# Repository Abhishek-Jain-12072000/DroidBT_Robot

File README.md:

# DROIDBT_Robot
 Self-propelled robot controlled via a dedicated application in Andoid system.

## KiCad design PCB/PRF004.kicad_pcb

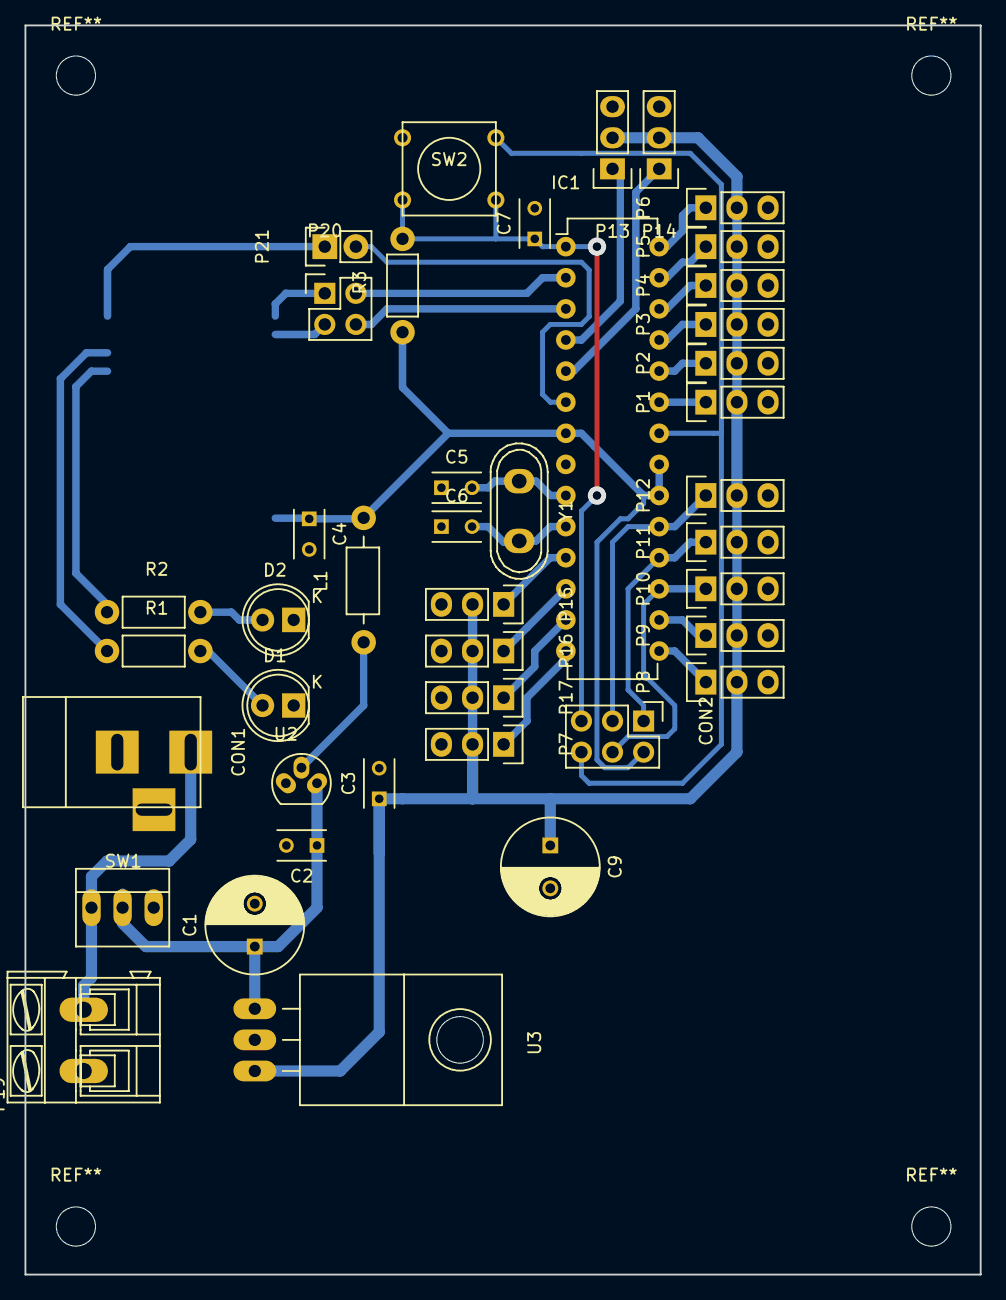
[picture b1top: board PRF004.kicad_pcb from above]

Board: 2 copper layers, 78.0 x 102.0 mm, 43 parts (1 on the bottom side), 36 nets.

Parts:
C1, C9: 470u; C_Radial_D8_L11.5_P3.5
C2, C3, C4, C7: 100n; C_Rect_L4_W2.5_P2.5
C5, C6: 22p; C_Rect_L4_W2.5_P2.5
CON1: BARREL_JACK
CON2: AVR-ISP-6; Pin_Header_Straight_2x03
D1, D2: LED; LED-5MM
IC1: ATMEGA8A-P; DIP-28_W7.62mm
L1: 10m; Choke_Horizontal_RM10mm
P1, P2, P3, P4, P5, P6, P7, P8, P9, P10, P11, P12, P13, P14, P15, P16, P17: CONN_01X03; Pin_Header_Straight_1x03
P19: CONN_01X02; AK300-2
P20: CONN_02X02; Pin_Header_Straight_2x02
P21: CONN_02X01; Pin_Header_Straight_1x02
R1, R2: 470; Resistor_Horizontal_RM7mm
R3: 4k7; Resistor_Horizontal_RM7mm
SW1: SPST; PINHEAD1-3
SW2: SW_PUSH; SW_PUSH_SMALL
U1: HC-05
U2: APE8865N-33-HF-3; TO-92_Molded_Narrow_Oval
U3: LM_7805; TO-220_Neutral123_Horizontal_LargePads
Y1: 16M; Crystal_HC50-U_Vertical

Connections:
+3V3: C4.1, CON2.2, IC1.7, IC1.20, IC1.21, L1.2, R3.1, U1.12
+5V: C3.1, C9.1, P1.2, P2.2, P3.2, P4.2, P5.2, P6.2, P7.2, P8.2, P9.2, P10.2, P11.2, P12.2, P13.2, P14.2, P15.2, P16.2, P17.2, U3.3
GND: C1.2, C2.2, C3.2, C4.2, C5.1, C6.1, C7.2, C9.2, CON1.2, CON1.3, CON2.6, D1.1, D2.1, IC1.8, IC1.22, P1.3, P2.3, P3.3, P4.3, P5.3, P6.3, P7.3, P8.3, P9.3, P10.3, P11.3, P12.3, P13.3, P14.3, P15.3, P16.3, P17.3, P19.1, SW2.1, U1.13, U1.21, U1.22, U2.1, U3.2
KEY: IC1.6, P21.2
MISO: CON2.1, IC1.18, P11.1
MOSI: CON2.4, IC1.17, P10.1
unnamed: C1.1, C2.1, SW1.2, U2.3, U3.1
unnamed: C5.2, IC1.9, Y1.1
unnamed: C6.2, IC1.10, Y1.2
unnamed: CON1.1, P19.2, SW1.1
unnamed: D1.2, R1.2
unnamed: D2.2, R2.2
unnamed: L1.1, U2.2
unnamed: P20.1, U1.1
unnamed: P20.3, U1.2
unnamed: P21.1, U1.34
unnamed: R1.1, U1.32
unnamed: R2.1, U1.31
PB0: IC1.14, P7.1
PB1: IC1.15, P8.1
PB2: IC1.16, P9.1
PC0: IC1.23, P1.1
PC1: IC1.24, P2.1
PC2: IC1.25, P3.1
PC3: IC1.26, P4.1
PC4: IC1.27, P5.1
PC5: IC1.28, P6.1
PD2: IC1.4, P13.1
PD3: IC1.5, P14.1
PD5: IC1.11, P15.1
PD6: IC1.12, P16.1
PD7: IC1.13, P17.1
RST: C7.1, CON2.5, IC1.1, R3.2, SW2.2
Rx_Bt: IC1.3, P20.4
SCK: CON2.3, IC1.19, P12.1
Tx_Bt: IC1.2, P20.2

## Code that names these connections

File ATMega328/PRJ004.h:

/*
 * PRJ004.h
 *
 *  Created on: 22-12-2015
 *      Author: rafau
 */

#ifndef PRJ004_H_
#define PRJ004_H_
#define F_CPU 8000000UL
#include <inttypes.h>
#include <avr/io.h>
#include <stdio.h>
#include <stdlib.h>
#include <util/delay.h>

//servo macros
#define SERVO_PERIOD		20000
#define SERVO_90			1500
#define SERVO_180			2600
#define SERVO_0				600
#define TIMER1_INIT_VAL		45535
#define SERVO_DDR			DDRB
#define SERVO_PORT			PORTB
#define SERVO_PING_DDR		DDRD
#define SERVO_PING_PORT		PORTD
#define SERVO_R				PB1
#define SERVO_L				PB2
#define SERVO_H				PD6
#define SERVO_V				PD5

//servo timer2 macros
#define SERVO_PERIOD_2		255
#define SERVO_90_2			16
#define SERVO_180_2			40
#define SERVO_0_2			8

#define PING_PORT	PORTD
#define PING_PIN	PIND
#define PING_DDR	DDRD
#define PING_P		PD3
#define PING_PCIE	PCIE2
#define PING_PCINT	PCINT19

typedef struct {
	int8_t left;
	int8_t right;
	uint8_t horizontal;
	uint8_t vertical;
	uint8_t arm;
	int32_t encoderLeft;
	int32_t encoderRight;
} Servo;

void counter0_init();
void timer1_init();
void timer2_init();
void setArmServo(Servo servo);
void getPingData();

uint16_t sensorRight();
uint16_t sensorCenter();
uint16_t sensorLeft();
int8_t lineError(uint16_t right, uint16_t center, uint16_t left);
int8_t PD(int error);

#endif /* PRJ004_H_ */

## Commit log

2017-04-19 first_commit
